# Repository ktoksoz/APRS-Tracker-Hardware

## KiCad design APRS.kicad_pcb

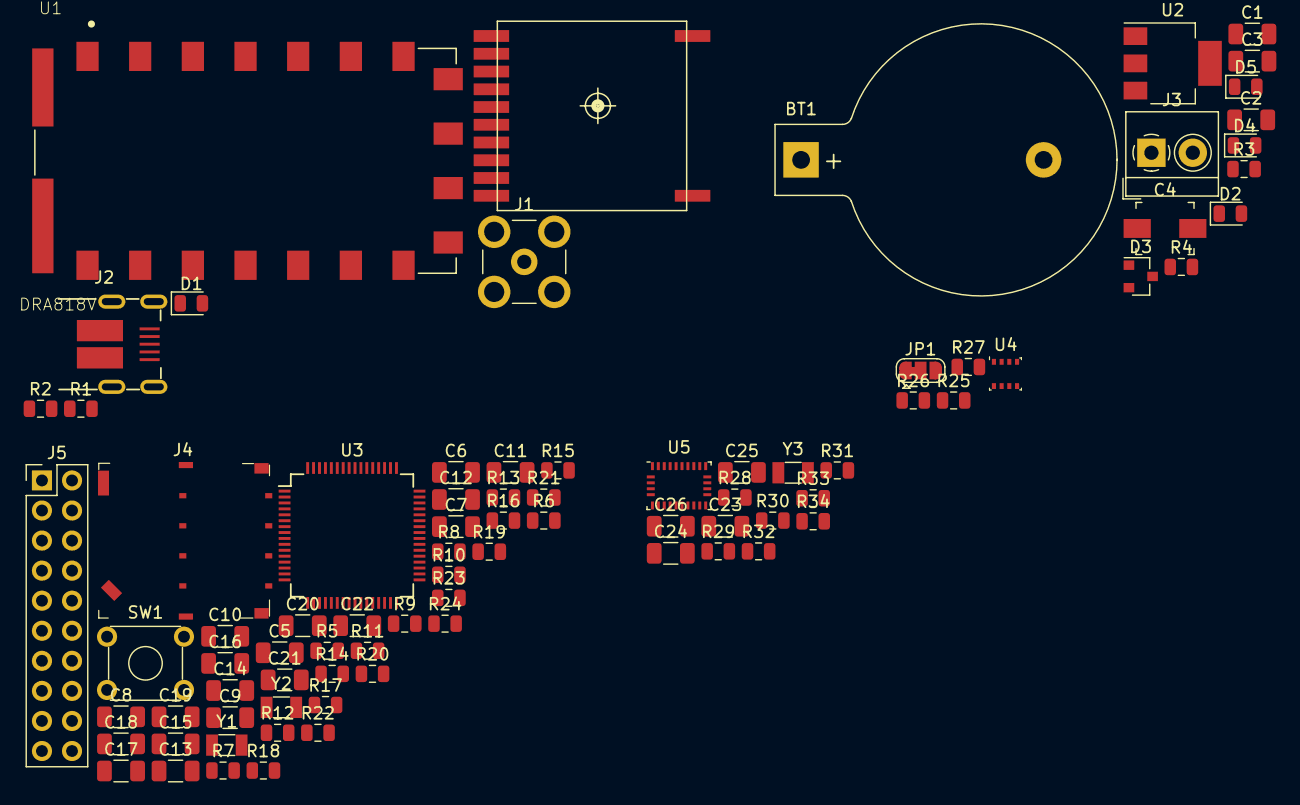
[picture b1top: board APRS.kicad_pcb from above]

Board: 2 copper layers, 82 parts (0 on the bottom side), 61 nets, no tracks yet.

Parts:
BT1: Battery_Cell; BatteryHolder_Keystone_103_1x20mm
C1, C2, C3: 2.2u; C_1206_3216Metric
C4: 100u; C_Trimmer_Murata_TZB4-A
C5, C10, C11: 2.2uF; C_1206_3216Metric
C6, C9: 1.5p; C_1206_3216Metric
C7, C8: 20p; C_1206_3216Metric
C12: 100nF; C_1206_3216Metric
C13, C14, C15, C16, C17, C18, C19, C20, C21, C22: 100n; C_1206_3216Metric
C23, C24: 0.1u; C_1206_3216Metric
C25, C26: 22p; C_1206_3216Metric
D1, D4, D5: LED; LED_0805_2012Metric
D2: D; D_0805_2012Metric
D3: BAT54C; SOT-23
G1: FGPMMOPA6B
J1: Conn_Coaxial; SMB_Jack_Vertical
J2: USB_B_Micro; USB_Micro_B_Male_UJ2-MIBH-4-SMT-TR
J3: Screw_Terminal_01x02; TerminalBlock_4Ucon_1x02_P3.50mm_Horizontal
J4: Micro_SD_Card; SD_Holder_787231001
J5: Conn_ARM_JTAG_SWD_20; PinHeader_2x10_P2.54mm_Vertical
JP1: SolderJumper_3_Bridged12; SolderJumper-3_P1.3mm_Bridged12_RoundedPad1.0x1.5mm
R1, R3, R4: 330; R_0805_2012Metric
R2, R5, R10, R11, R12, R13, R14, R15, R16, R17, R18, R19, R20, R21, R22, R23, R24, R25, R26, R27, R28, R29, R30, R31, R32, R33, R34: 10k; R_0805_2012Metric
R6, R7, R8, R9: 0; R_0805_2012Metric
SW1: SW_Push; SW_TH_Tactile_Omron_B3F-10xx
U1: DRA818V; DORJI_DRA818V
U2: AMS1117-3.3; SOT-223-3_TabPin2
U3: STM32F405RGTx; LQFP-64_10x10mm_P0.5mm
U4: BME280; Bosch_LGA-8_2.5x2.5mm_P0.65mm_ClockwisePinNumbering
U5: BNO055; LGA-28_5.2x3.8mm_P0.5mm
Y1: 32.768khz; Crystal_SMD_3215-2Pin_3.2x1.5mm
Y2: 25MHz; Crystal_SMD_3215-2Pin_3.2x1.5mm
Y3: 32.768kHz; Crystal_SMD_3215-2Pin_3.2x1.5mm

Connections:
+5V: C1.1, C2.1, D2.1, U1.8, U2.3
+BATT: D3.3, U3.1
/3D_FIX: R1.2, U3.24
/ADC_IN: C12.1, U1.3
/CPU/NRST: C5.2, J5.15, R5.1, SW1.1, U3.7
/CPU/SDIO_CK: J4.5, R13.1, U3.53
/CPU/SDIO_CMD: J4.3, R14.1, U3.54
/CPU/SDIO_D0: J4.7, R12.1, U3.39
/CPU/SDIO_D1: J4.8, R10.1, U3.40
/CPU/SDIO_D2: J4.1, R16.1, U3.51
/CPU/SDIO_D3: J4.2, R15.1, U3.52
/CPU/SWDCLK: J5.9, R23.2, U3.49
/CPU/SWDIO: J5.7, R17.1, U3.46
/CPU/SWO: J5.13, R18.1, U3.55
/CPU/TDI: J5.5, R19.1, U3.50
/CPU/TRST: J5.3, R21.1, U3.56
/DAC_OUT1: U1.18, U3.20
/I2C_SCL: R26.2, R28.2, U3.61, U4.4, U5.19
/I2C_SDA: R27.2, R29.2, U3.59, U4.3, U5.20
/IMU_ADR: U3.58, U5.17
/IMU_INT: R31.2, U3.57, U5.14
/RADIO_ENABLE: U1.6, U3.8
/RADIO_PTT: U1.5, U3.15
/RADIO_PWR: U1.7, U3.25
/RADIO_RX: U1.17, U3.17
/RADIO_TX: U1.16, U3.16
/USB_DM: J2.2, U3.44
/USB_DP: J2.3, U3.45
GND: BT1.2, C1.2, C2.2, C3.2, C4.2, C5.1, C6.1, C7.1, C8.1, C9.1, C10.1, C11.1, C13.1, C14.1, C15.1, C16.1, C17.1, C18.1, C19.1, C20.1, C21.1, C22.1, C23.1, C24.1, C25.1, C26.1, D1.1, J1.2, J2.5, J3.1, J4.6, J4.9, J5.4, J5.6, J5.8, J5.10, J5.12, J5.14, J5.16, J5.18, J5.20, JP1.2, R2.2, R3.2, R4.2, R11.2, R20.1, R22.1, R23.1, R24.2, R33.2, R34.2, SW1.2, U1.9, U1.10, U2.1, U3.12, U3.18, U3.63, U4.1, U4.7, U5.2, U5.10, U5.15, U5.16, U5.18, U5.25
unnamed: BT1.1, D3.1, D4.2
unnamed: C6.2, R8.1, Y1.1
unnamed: C7.2, R6.2, Y2.1
unnamed: C8.2, R7.2, Y2.2
unnamed: C9.2, R9.2, Y1.2
unnamed: C10.2, U3.31
unnamed: C11.2, U3.47
unnamed: C12.2, U3.14
unnamed: C24.2, U5.9
unnamed: C25.2, U5.26, Y3.1
unnamed: C26.2, U5.27, Y3.2
unnamed: D1.2, R1.1
unnamed: D2.2, J3.2
unnamed: D4.1, R3.1
unnamed: D5.1, R4.1
unnamed: J1.1, U1.12
unnamed: J2.4, R2.1
unnamed: J5.11, R24.1
unnamed: J5.17, R20.2
unnamed: J5.19, R22.2
unnamed: JP1.1, R25.1
unnamed: R6.1, U3.5
unnamed: R7.1, U3.6
unnamed: R8.2, U3.3
unnamed: R9.1, U3.4
unnamed: R11.1, U3.60
unnamed: R25.2, U4.5
unnamed: R30.2, U5.4
unnamed: R32.2, U5.11
unnamed: R33.1, U5.5
unnamed: R34.1, U5.6
VDD: C3.1, C4.1, C13.2, C14.2, C15.2, C16.2, C17.2, C18.2, C19.2, C20.2, C21.2, C22.2, C23.2, D3.2, D5.2, J4.4, J5.1, J5.2, JP1.3, R5.2, R10.2, R12.2, R13.2, R14.2, R15.2, R16.2, R17.2, R18.2, R19.2, R21.2, R26.1, R27.1, R28.1, R29.1, R30.1, R31.1, R32.1, U2.2, U3.13, U3.19, U3.32, U3.48, U3.64, U4.2, U4.6, U4.8, U5.3, U5.28
